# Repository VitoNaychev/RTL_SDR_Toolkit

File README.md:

# RTL_SDR_Toolkit
A command line toolkit for the RTL-SDR

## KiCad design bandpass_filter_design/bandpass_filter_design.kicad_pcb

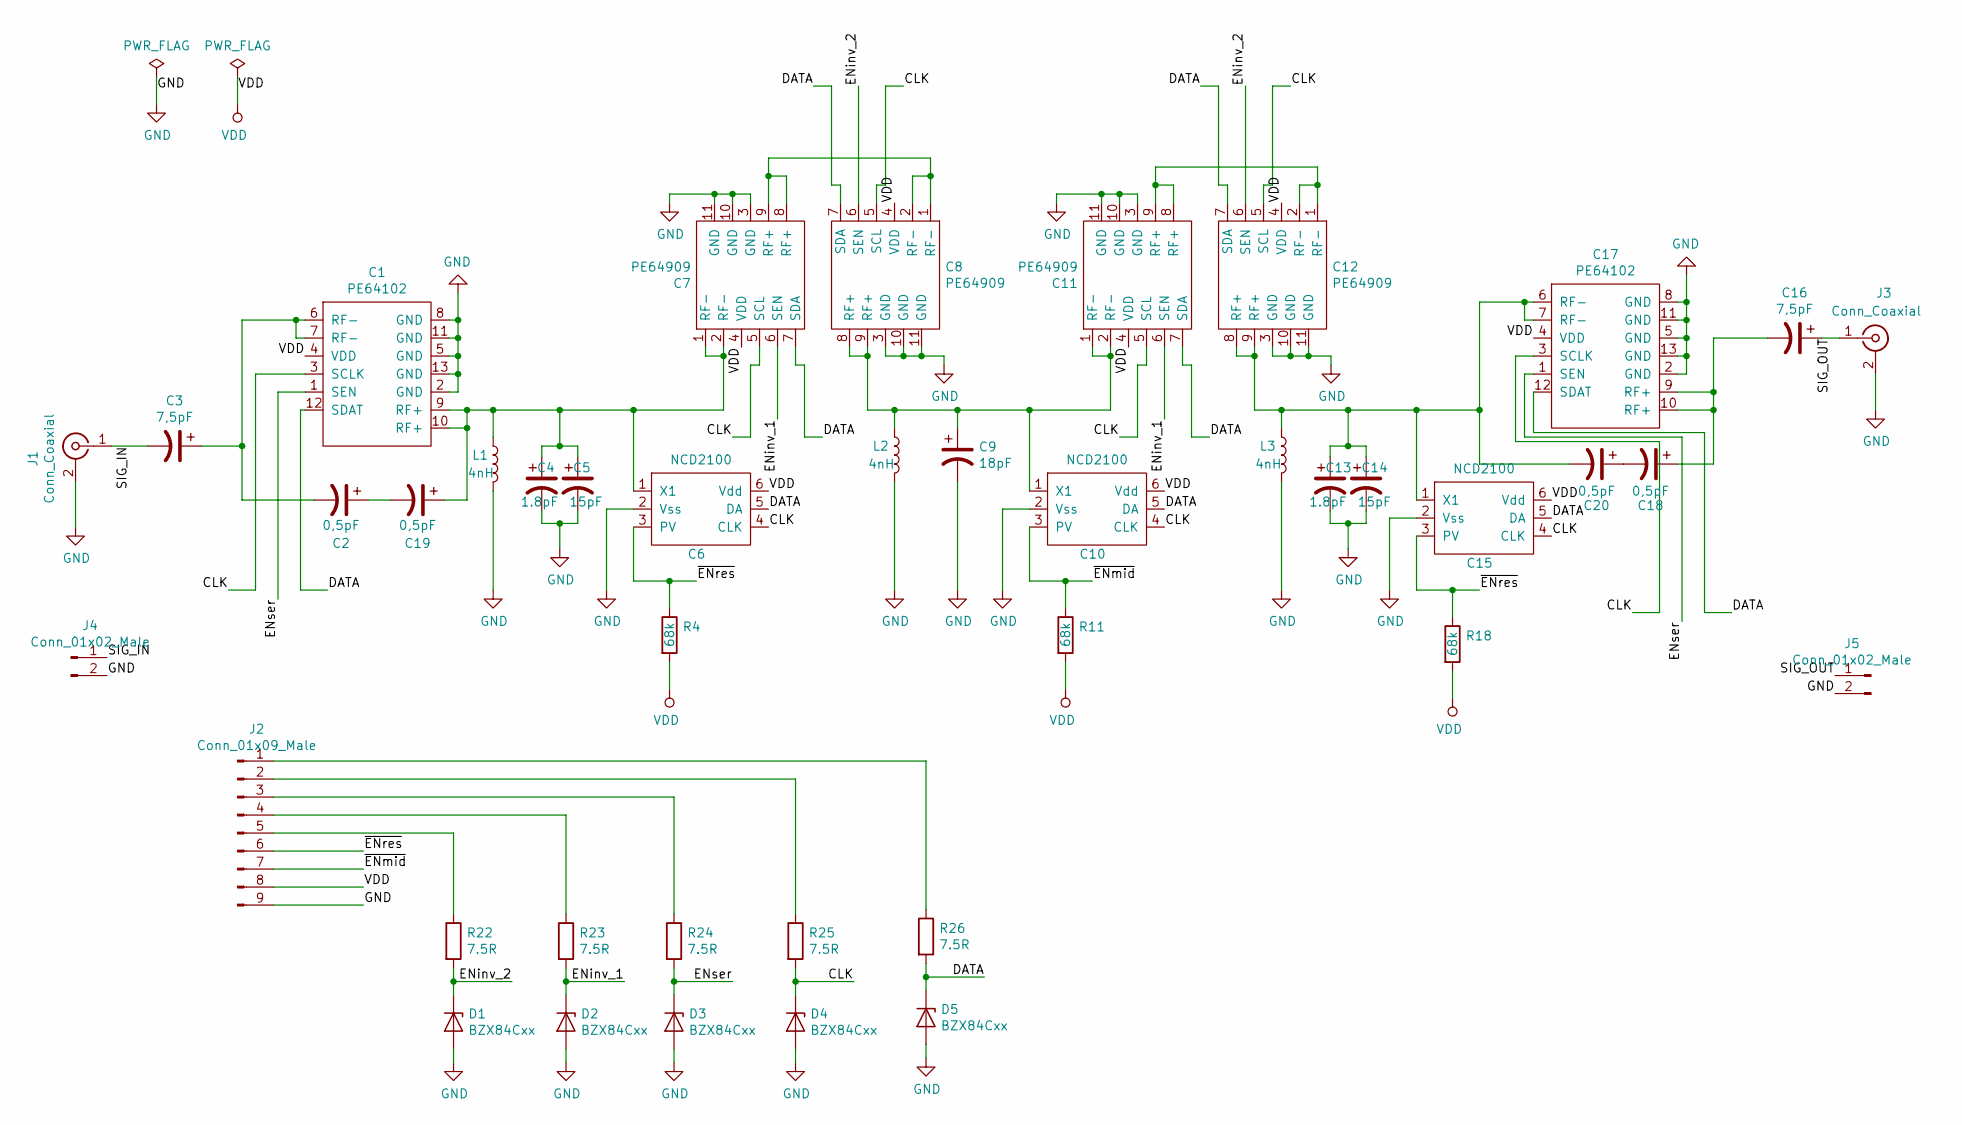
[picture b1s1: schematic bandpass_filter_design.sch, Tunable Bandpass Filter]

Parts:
C1, C17: PE64102; PE64102-QFN
C2, C18, C19, C20: 0,5pF; C_0805_2012Metric_Pad1.15x1.40mm_HandSolder
C3, C16: 7,5pF; C_0805_2012Metric_Pad1.15x1.40mm_HandSolder
C4, C13: 1.8pF; C_0805_2012Metric_Pad1.15x1.40mm_HandSolder
C5, C14: 15pF; C_0805_2012Metric_Pad1.15x1.40mm_HandSolder
C6, C10, C15: NCD2100; NCD2100-TSOT-6
C7, C8, C11, C12: PE64909; PE64909-QFN
C9: 18pF; C_0805_2012Metric_Pad1.15x1.40mm_HandSolder
D1, D2, D3, D4, D5: BZX84Cxx; D_SOT-23_ANK
J1, J3: Conn_Coaxial; SMA_Amphenol_901-144_Vertical
J2: Conn_01x09_Male; PinHeader_1x09_P2.54mm_Vertical
J4, J5: Conn_01x02_Male; PinHeader_1x02_P2.54mm_Vertical
L1, L2, L3: 4nH; L_0402_1005Metric
R4, R11, R18: 68k; R_0805_2012Metric_Pad1.15x1.40mm_HandSolder
R22, R23, R24, R25, R26: 7.5R; R_0805_2012Metric_Pad1.15x1.40mm_HandSolder

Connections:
/CLK: C1.3 (SCLK), C6.4 (CLK), C7.5 (SCL), C8.5 (SCL), C10.4 (CLK), C11.5 (SCL), C12.5 (SCL), C15.4 (CLK), C17.3 (SCLK), D4.1 (K), R25.2
/DATA: C1.12 (SDAT), C6.5 (DA), C7.7 (SDA), C8.7 (SDA), C10.5 (DA), C11.7 (SDA), C12.7 (SDA), C15.5 (DA), C17.12 (SDAT), D5.1 (K), R26.2
/ENinv_1: C7.6 (SEN), C11.6 (SEN), D2.1 (K), R23.2
/ENinv_2: C8.6 (SEN), C12.6 (SEN), D1.1 (K), R22.2
/ENser: C1.1 (SEN), C17.1 (SEN), D3.1 (K), R24.2
/SIG_IN: C3.2, J1.1 (In), J4.1
/SIG_OUT: C16.1, J3.1 (In), J5.1
/~ENmid: C10.3 (PV), J2.7, R11.1
/~ENres: C6.3 (PV), C15.3 (PV), J2.6, R4.1, R18.1
GND: C1.2 (GND), C1.5 (GND), C1.8 (GND), C1.11 (GND), C1.13 (GND), C4.2, C5.2, C6.2 (Vss), C7.3 (GND), C7.10 (GND), C7.11 (GND), C8.3 (GND), C8.10 (GND), C8.11 (GND), C9.2, C10.2 (Vss), C11.3 (GND), C11.10 (GND), C11.11 (GND), C12.3 (GND), C12.10 (GND), C12.11 (GND), C13.2, C14.2, C15.2 (Vss), C17.2 (GND), C17.5 (GND), C17.8 (GND), C17.11 (GND), C17.13 (GND), D1.2 (A), D2.2 (A), D3.2 (A), D4.2 (A), D5.2 (A), J1.2 (Ext), J2.9, J3.2 (Ext), J4.2, J5.2, L1.2, L2.2, L3.2
unnamed: C1.6 (RF-), C1.7 (RF-), C2.2, C3.1
unnamed: C1.9 (RF+), C1.10 (RF+), C4.1, C5.1, C6.1 (X1), C7.1 (RF-), C7.2 (RF-), C19.1, L1.1
unnamed: C7.8 (RF+), C7.9 (RF+), C8.1 (RF-), C8.2 (RF-)
unnamed: C8.8 (RF+), C8.9 (RF+), C9.1, C10.1 (X1), C11.1 (RF-), C11.2 (RF-), L2.1
unnamed: C11.8 (RF+), C11.9 (RF+), C12.1 (RF-), C12.2 (RF-)
unnamed: C12.8 (RF+), C12.9 (RF+), C13.1, C14.1, C15.1 (X1), C17.6 (RF-), C17.7 (RF-), C20.2, L3.1
unnamed: C16.2, C17.9 (RF+), C17.10 (RF+), C18.1
unnamed: C18.2, C20.1
unnamed: C2.1, C19.2
unnamed: J2.1, R26.1
unnamed: J2.2, R25.1
unnamed: J2.3, R24.1
unnamed: J2.4, R23.1
unnamed: J2.5, R22.1
VDD: C1.4 (VDD), C6.6 (Vdd), C7.4 (VDD), C8.4 (VDD), C10.6 (Vdd), C11.4 (VDD), C12.4 (VDD), C15.6 (Vdd), C17.4 (VDD), J2.8, R4.2, R11.2, R18.2

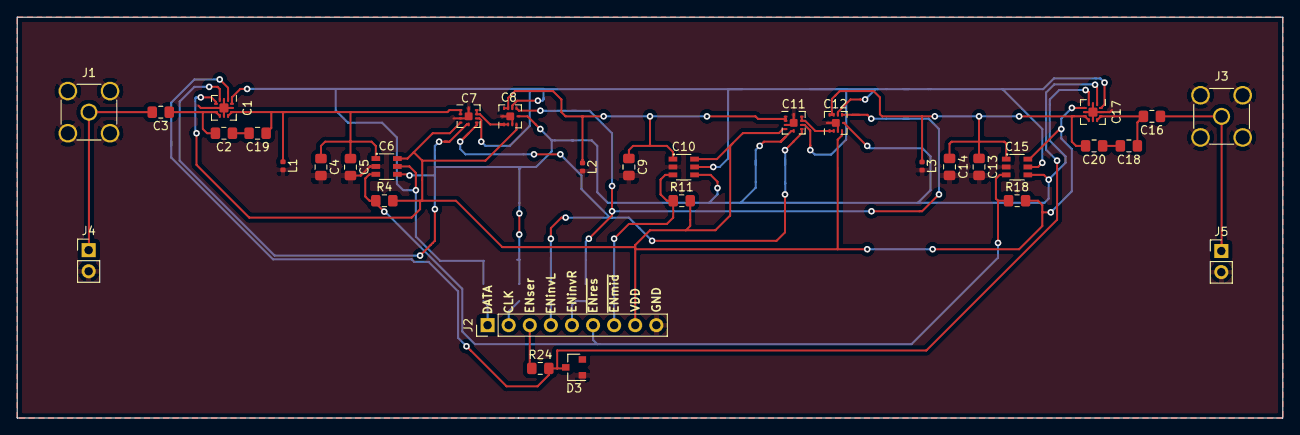
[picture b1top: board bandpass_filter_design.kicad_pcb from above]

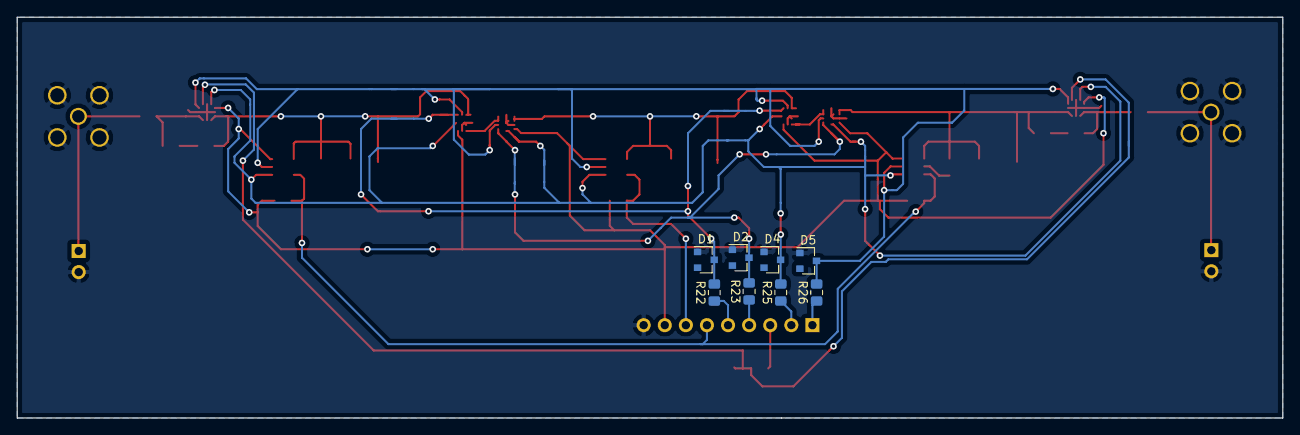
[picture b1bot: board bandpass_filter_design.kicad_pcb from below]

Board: 2 copper layers, 152.4 x 48.3 mm, 41 parts (8 on the bottom side), 25 nets.

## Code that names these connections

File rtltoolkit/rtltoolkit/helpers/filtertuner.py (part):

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#
# Pin 0 - DATA
# Pin 1 - CLK
# Pin 2 - ENser (Enable series capacitor)
# Pin 3 - ENinvL (Enable left inverter capacitor)
# Pin 4 - ENinvR (Enable right inverter capacitor)
# Pin 5 - ~ENres (Enable outer resonators)
# Pin 6 - ~ENmid (Enable middle resonator)
# Pin 7 - Vdd
# Pin 8 - GND
#
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#
# Pin 19 - DATA
# Pin 23 - CLK
# Pin 29 - ENser
# Pin 31 - ENinvL
# Pin 33 - ENinvR
# Pin 35 - ~ENres
# Pin 37 - ~ENmid
# Pin  1 - Vdd (3.3 V)
# Pin 39 - GND
#
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    BANDWIDTH = 5e6
    L = [4e-9, 4e-9, 4e-9]

    ENser_PIN = 29
    ENinvL_PIN = 31
    ENinvR_PIN = 33
    ENres_PIN = 35
    ENmid_PIN = 37

    INVERTER_COMBS = {}

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        pe64102_actual += CAP_PAR
        series_actual = (pe64102_actual * CAP_SER) / (pe64102_actual + CAP_SER)

        # transmit_PE64xxx(spi, FilterTuner.ENser_PIN, pe64102_code)
        return series_actual

    def tune_resonator(req_value, spi):
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        # Calculate the outter resonators value
        resonator_actual = ncd2100_actual + RES_PAR

        # transmit_NCD2100(spi, FilterTuner.ENres_PIN, ncd2100_code)
        return resonator_actual

    def tune_middle(req_value, spi):
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        # Calculate the middle resonator value
        middle_actual = ncd2100_value + MID_PAR

        # transmit_NCD2100(spi, FilterTuner.ENmid_PIN, ncd2100_code)
        return middle_actual

    def init_GPIOs():
        GPIO.setmode(GPIO.BOARD)
        GPIO.setup(FilterTuner.ENser_PIN, GPIO.OUT)
        GPIO.output(FilterTuner.ENser_PIN, False)
        GPIO.setup(FilterTuner.ENinvL_PIN, GPIO.OUT)
        GPIO.output(FilterTuner.ENinvL_PIN, False)
        GPIO.setup(FilterTuner.ENinvR_PIN, GPIO.OUT)
        GPIO.output(FilterTuner.ENinvR_PIN, False)
        GPIO.setup(FilterTuner.ENres_PIN, GPIO.OUT)
        GPIO.output(FilterTuner.ENres_PIN, True)
        GPIO.setup(FilterTuner.ENmid_PIN, GPIO.OUT)
        GPIO.output(FilterTuner.ENmid_PIN, True)

    def init_SPI(self):
        spi = spidev.SpiDev()
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
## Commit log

2019-01-14 init commit
2019-01-14 Fix TempDemod sample cutting
2019-01-14 New base class for the demodulators and save to file option
2019-01-17 Added command line args
2019-02-01 About to refactor
2019-02-03 Refactor + FM specter scan function
2019-02-05 record samples command line
2019-02-05 fm scan working and method run in base class
2019-02-06 ADS-B deomdulation to hex and description of demod process
2019-02-06 Added gitignore
2019-02-06 Remove useless temp_data.npy
2019-02-12 Begin filter design
2019-02-12 Gitignore update
2019-02-12 ASCII art FFT(not tested)
2019-02-17 Bandpass filter done
2019-02-18 Create transmit, jammer and replay task
2019-03-10 Prerefactor
2019-03-18 Big refactor and updated FFT sink look
2019-03-19 Refactor FM Demod and add Power to Scan FM
2019-04-22 Pre-module commit
2019-04-22 Create package for the whole toolkit with new direcotry structure
2019-05-08 ADS-B decode working and some fixes
2019-05-16 AdsbDemod class refactor
2019-05-18 Add new methods for tuning the filter
2019-05-27 Transmit tasks working
2019-05-27 Replace asyncio with rtl_sdr and multiprocessing
2019-05-30 Scan-FM working with new implementation
2019-05-30 TempDemod time constatnts added
2019-05-30 Custom tune FM demod implemetation added
2019-06-06 FilterDesign class works
2019-06-06 No random multiplication by 360 and fix delta
2019-06-06 Filter configuration in TransmitTask
